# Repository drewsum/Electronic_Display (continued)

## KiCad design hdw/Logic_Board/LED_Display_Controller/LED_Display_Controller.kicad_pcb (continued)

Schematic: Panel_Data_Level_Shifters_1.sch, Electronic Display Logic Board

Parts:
C2601, C2602: 0.1uF; C_0603; Voltage 50V; Digi-Key PN 311-1344-1-ND
C2603, C2604: 10nF; C_0603; Voltage 50V; Digi-Key PN 1276-1921-1-ND
C2605, C2606: 1nF; C_0603; Voltage 50V; Digi-Key PN 1276-1018-1-ND
R2601, R2602, R2603, R2604, R2605, R2606, R2607, R2608, R2609, R2610, R2611, R2612, R2643, R2644, R2645, R2646, R2647, R2648, R2649, R2650, R2651, R2652, R2653, R2654: 100; R_0603; Tolerance 1%; Digi-Key PN A106047CT-ND
R2613, R2614, R2615, R2616, R2617, R2618, R2619, R2620, R2621, R2622, R2623, R2624, R2625, R2626, R2627, R2628, R2629, R2630, R2631, R2632, R2633, R2634, R2635, R2636, R2637, R2638, R2639, R2640, R2641, R2642: 10K; R_0603; Tolerance 1%; Digi-Key PN RMCF0603FT10K0CT-ND
U2601, U2602: 74HCT541; TSSOP-20_4.4x6.5mm_Pitch0.65mm; Digi-Key PN 296-26499-1-ND

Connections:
+3V3: R2613.1, R2614.1; also elsewhere on the board
+5V: C2601.1, C2602.1, C2603.1, C2604.1, C2605.1, C2606.1, U2601.20 (VCC), U2602.20 (VCC); also elsewhere on the board
B0_POS3P3: R2604.1; also elsewhere on the board
B0_POS5: R2646.1; also elsewhere on the board
B1_POS3P3: R2601.1; also elsewhere on the board
B1_POS5: R2643.1; also elsewhere on the board
B2_POS3P3: R2610.1; also elsewhere on the board
B2_POS5: R2652.1; also elsewhere on the board
B3_POS3P3: R2607.1; also elsewhere on the board
B3_POS5: R2649.1; also elsewhere on the board
G0_POS3P3: R2605.1; also elsewhere on the board
G0_POS5: R2647.1; also elsewhere on the board
G1_POS3P3: R2602.1; also elsewhere on the board
G1_POS5: R2644.1; also elsewhere on the board
G2_POS3P3: R2611.1; also elsewhere on the board
G2_POS5: R2653.1; also elsewhere on the board
G3_POS3P3: R2608.1; also elsewhere on the board
G3_POS5: R2650.1; also elsewhere on the board
GND: C2601.2, C2602.2, C2603.2, C2604.2, C2605.2, C2606.2, R2615.2, R2616.2, R2617.2, R2618.2, R2619.2, R2620.2, R2621.2, R2622.2, R2623.2, R2624.2, R2625.2, R2626.2, R2627.2, R2628.2, R2629.2, R2630.2, R2631.2, R2632.2, R2633.2, R2634.2, R2635.2, R2636.2, R2637.2, R2638.2, R2639.2, R2640.2, R2641.2, R2642.2, U2601.10 (GND), U2602.10 (GND); also elsewhere on the board
unnamed: R2601.2, R2615.1, U2601.2 (A0)
unnamed: R2602.2, R2617.1, U2601.3 (A1)
unnamed: R2603.2, R2619.1, U2601.4 (A2)
unnamed: R2604.2, R2621.1, U2601.5 (A3)
unnamed: R2605.2, R2623.1, U2601.6 (A4)
unnamed: R2606.2, R2625.1, U2601.7 (A5)
unnamed: R2607.2, R2616.1, U2602.2 (A0)
unnamed: R2608.2, R2618.1, U2602.3 (A1)
unnamed: R2609.2, R2620.1, U2602.4 (A2)
unnamed: R2610.2, R2622.1, U2602.5 (A3)
unnamed: R2611.2, R2624.1, U2602.6 (A4)
unnamed: R2612.2, R2626.1, U2602.7 (A5)
unnamed: R2627.1, U2601.8 (A6)
unnamed: R2628.1, U2602.8 (A6)
unnamed: R2629.1, U2601.9 (A7)
unnamed: R2630.1, U2602.9 (A7)
unnamed: R2631.1, R2648.2, U2601.13 (Y5)
unnamed: R2632.1, R2654.2, U2602.13 (Y5)
unnamed: R2633.1, R2647.2, U2601.14 (Y4)
unnamed: R2634.1, R2653.2, U2602.14 (Y4)
unnamed: R2635.1, R2646.2, U2601.15 (Y3)
unnamed: R2636.1, R2652.2, U2602.15 (Y3)
unnamed: R2637.1, R2645.2, U2601.16 (Y2)
unnamed: R2638.1, R2651.2, U2602.16 (Y2)
unnamed: R2639.1, R2644.2, U2601.17 (Y1)
unnamed: R2640.1, R2650.2, U2602.17 (Y1)
unnamed: R2641.1, R2643.2, U2601.18 (Y0)
unnamed: R2642.1, R2649.2, U2602.18 (Y0)
R0_POS3P3: R2606.1; also elsewhere on the board
R0_POS5: R2648.1; also elsewhere on the board
R1_POS3P3: R2603.1; also elsewhere on the board
R1_POS5: R2645.1; also elsewhere on the board
R2_POS3P3: R2612.1; also elsewhere on the board
R2_POS5: R2654.1; also elsewhere on the board
R3_POS3P3: R2609.1; also elsewhere on the board
R3_POS5: R2651.1; also elsewhere on the board
~LVL_SHFT_EN: R2613.2, R2614.2, U2601.1 (G1), U2601.19 (G2), U2602.1 (G1), U2602.19 (G2); also elsewhere on the board

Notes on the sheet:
26. Panel Data Level Shifters 1

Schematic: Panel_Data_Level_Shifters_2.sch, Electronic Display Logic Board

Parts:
C2701, C2702: 0.1uF; C_0603; Voltage 50V; Digi-Key PN 311-1344-1-ND
C2703, C2704: 10nF; C_0603; Voltage 50V; Digi-Key PN 1276-1921-1-ND
C2705, C2706: 1nF; C_0603; Voltage 50V; Digi-Key PN 1276-1018-1-ND
R2701, R2702, R2703, R2704, R2705, R2706, R2707, R2708, R2709, R2710, R2711, R2712, R2743, R2744, R2745, R2746, R2747, R2748, R2749, R2750, R2751, R2752, R2753, R2754: 100; R_0603; Tolerance 1%; Digi-Key PN A106047CT-ND
R2713, R2714, R2715, R2716, R2717, R2718, R2719, R2720, R2721, R2722, R2723, R2724, R2725, R2726, R2727, R2728, R2729, R2730, R2731, R2732, R2733, R2734, R2735, R2736, R2737, R2738, R2739, R2740, R2741, R2742: 10K; R_0603; Tolerance 1%; Digi-Key PN RMCF0603FT10K0CT-ND
U2701, U2702: 74HCT541; TSSOP-20_4.4x6.5mm_Pitch0.65mm; Digi-Key PN 296-26499-1-ND

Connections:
+3V3: R2713.1, R2714.1; also elsewhere on the board
+5V: C2701.1, C2702.1, C2703.1, C2704.1, C2705.1, C2706.1, U2701.20 (VCC), U2702.20 (VCC); also elsewhere on the board
B4_POS3P3: R2704.1; also elsewhere on the board
B4_POS5: R2746.1; also elsewhere on the board
B5_POS3P3: R2701.1; also elsewhere on the board
B5_POS5: R2743.1; also elsewhere on the board
B6_POS3P3: R2710.1; also elsewhere on the board
B6_POS5: R2752.1; also elsewhere on the board
B7_POS3P3: R2707.1; also elsewhere on the board
B7_POS5: R2749.1; also elsewhere on the board
G4_POS3P3: R2705.1; also elsewhere on the board
G4_POS5: R2747.1; also elsewhere on the board
G5_POS3P3: R2702.1; also elsewhere on the board
G5_POS5: R2744.1; also elsewhere on the board
G6_POS3P3: R2711.1; also elsewhere on the board
G6_POS5: R2753.1; also elsewhere on the board
G7_POS3P3: R2708.1; also elsewhere on the board
G7_POS5: R2750.1; also elsewhere on the board
GND: C2701.2, C2702.2, C2703.2, C2704.2, C2705.2, C2706.2, R2715.2, R2716.2, R2717.2, R2718.2, R2719.2, R2720.2, R2721.2, R2722.2, R2723.2, R2724.2, R2725.2, R2726.2, R2727.2, R2728.2, R2729.2, R2730.2, R2731.2, R2732.2, R2733.2, R2734.2, R2735.2, R2736.2, R2737.2, R2738.2, R2739.2, R2740.2, R2741.2, R2742.2, U2701.10 (GND), U2702.10 (GND); also elsewhere on the board
unnamed: R2701.2, R2715.1, U2701.2 (A0)
unnamed: R2702.2, R2717.1, U2701.3 (A1)
unnamed: R2703.2, R2719.1, U2701.4 (A2)
unnamed: R2704.2, R2721.1, U2701.5 (A3)
unnamed: R2705.2, R2723.1, U2701.6 (A4)
unnamed: R2706.2, R2725.1, U2701.7 (A5)
unnamed: R2707.2, R2716.1, U2702.2 (A0)
unnamed: R2708.2, R2718.1, U2702.3 (A1)
unnamed: R2709.2, R2720.1, U2702.4 (A2)
unnamed: R2710.2, R2722.1, U2702.5 (A3)
unnamed: R2711.2, R2724.1, U2702.6 (A4)
unnamed: R2712.2, R2726.1, U2702.7 (A5)
unnamed: R2727.1, U2701.8 (A6)
unnamed: R2728.1, U2702.8 (A6)
unnamed: R2729.1, U2701.9 (A7)
unnamed: R2730.1, U2702.9 (A7)
unnamed: R2731.1, R2748.2, U2701.13 (Y5)
unnamed: R2732.1, R2754.2, U2702.13 (Y5)
unnamed: R2733.1, R2747.2, U2701.14 (Y4)
unnamed: R2734.1, R2753.2, U2702.14 (Y4)
unnamed: R2735.1, R2746.2, U2701.15 (Y3)
unnamed: R2736.1, R2752.2, U2702.15 (Y3)
unnamed: R2737.1, R2745.2, U2701.16 (Y2)
unnamed: R2738.1, R2751.2, U2702.16 (Y2)
unnamed: R2739.1, R2744.2, U2701.17 (Y1)
unnamed: R2740.1, R2750.2, U2702.17 (Y1)
unnamed: R2741.1, R2743.2, U2701.18 (Y0)
unnamed: R2742.1, R2749.2, U2702.18 (Y0)
R4_POS3P3: R2706.1; also elsewhere on the board
R4_POS5: R2748.1; also elsewhere on the board
R5_POS3P3: R2703.1; also elsewhere on the board
R5_POS5: R2745.1; also elsewhere on the board
R6_POS3P3: R2712.1; also elsewhere on the board
R6_POS5: R2754.1; also elsewhere on the board
R7_POS3P3: R2709.1; also elsewhere on the board
R7_POS5: R2751.1; also elsewhere on the board
~LVL_SHFT_EN: R2713.2, R2714.2, U2701.1 (G1), U2701.19 (G2), U2702.1 (G1), U2702.19 (G2); also elsewhere on the board

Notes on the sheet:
27. Panel Data Level Shifters 2

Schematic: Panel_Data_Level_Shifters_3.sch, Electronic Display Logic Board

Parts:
C2801, C2802: 0.1uF; C_0603; Voltage 50V; Digi-Key PN 311-1344-1-ND
C2803: 10nF; C_0603; Voltage 50V; Digi-Key PN 1276-1921-1-ND
C2804: 1nF; C_0603; Voltage 50V; Digi-Key PN 1276-1018-1-ND
R2801, R2802, R2805, R2806, R2807, R2808, R2809, R2810, R2811, R2812, R2830, R2831, R2832, R2833, R2834, R2835, R2836, R2837: 100; R_0603; Tolerance 1%; Digi-Key PN A106047CT-ND
R2803, R2804: 10k; R_0603; Tolerance 1%; Digi-Key PN RMCF0603FT10K0CT-ND
R2813, R2814, R2815, R2816, R2817, R2818, R2819, R2820, R2821, R2822, R2823, R2824, R2825, R2826, R2827, R2828, R2829: 10K; R_0603; Tolerance 1%; Digi-Key PN RMCF0603FT10K0CT-ND
U2801: 74LVC1G32; SOT-353_SC-70-5; Digi-Key PN 296-9848-1-ND
U2802: 74HCT541; TSSOP-20_4.4x6.5mm_Pitch0.65mm; Digi-Key PN 296-26499-1-ND

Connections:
+3V3: C2801.1, R2803.1, R2813.1, R2814.1, R2815.1, U2801.5 (VCC); also elsewhere on the board
+5V: C2802.1, C2803.1, C2804.1, R2828.1, R2829.1, U2802.20 (VCC); also elsewhere on the board
GND: C2801.2, C2802.2, C2803.2, C2804.2, R2804.2, R2816.2, R2817.2, R2818.2, R2819.2, R2820.2, R2821.2, R2822.2, R2823.2, R2824.2, R2825.2, R2826.2, R2827.2, U2801.3 (GND), U2802.10 (GND); also elsewhere on the board
unnamed: R2801.2, R2803.2, U2801.1
unnamed: R2802.2, R2804.1, U2801.2
unnamed: R2805.2, R2814.2, U2802.2 (A0)
unnamed: R2806.2, R2815.2, U2802.3 (A1)
unnamed: R2807.2, R2816.1, U2802.4 (A2)
unnamed: R2808.2, R2817.1, U2802.5 (A3)
unnamed: R2809.2, R2818.1, U2802.6 (A4)
unnamed: R2810.2, R2819.1, U2802.7 (A5)
unnamed: R2811.2, R2820.1, U2802.8 (A6)
unnamed: R2812.2, R2821.1, U2802.9 (A7)
unnamed: R2822.1, R2837.2, U2802.11 (Y7)
unnamed: R2823.1, R2836.2, U2802.12 (Y6)
unnamed: R2824.1, R2835.2, U2802.13 (Y5)
unnamed: R2825.1, R2834.2, U2802.14 (Y4)
unnamed: R2826.1, R2833.2, U2802.15 (Y3)
unnamed: R2827.1, R2832.2, U2802.16 (Y2)
unnamed: R2828.2, R2831.2, U2802.17 (Y1)
unnamed: R2829.2, R2830.2, U2802.18 (Y0)
Panel_CLK_POS3P3: R2807.1; also elsewhere on the board
Panel_CLK_POS5: R2832.1; also elsewhere on the board
Panel_Dim_PWM: R2802.1; also elsewhere on the board
Panel_LAT_POS3P3: R2806.1; also elsewhere on the board
Panel_LAT_POS5: R2831.1; also elsewhere on the board
Row_A_POS3P3: R2811.1; also elsewhere on the board
Row_A_POS5: R2836.1; also elsewhere on the board
Row_B_POS3P3: R2810.1; also elsewhere on the board
Row_B_POS5: R2835.1; also elsewhere on the board
Row_C_POS3P3: R2809.1; also elsewhere on the board
Row_C_POS5: R2834.1; also elsewhere on the board
Row_D_POS3P3: R2808.1; also elsewhere on the board
Row_D_POS5: R2833.1; also elsewhere on the board
Row_E_POS3P3: R2812.1; also elsewhere on the board
Row_E_POS5: R2837.1; also elsewhere on the board
~LVL_SHFT_EN: R2813.2, U2802.1 (G1), U2802.19 (G2); also elsewhere on the board
~Panel_OE_Dim_POS3P3: R2805.1, U2801.4
~Panel_OE_POS3P3: R2801.1; also elsewhere on the board
~Panel_OE_POS5: R2830.1; also elsewhere on the board

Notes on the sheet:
28. Panel Data Level Shifters 3

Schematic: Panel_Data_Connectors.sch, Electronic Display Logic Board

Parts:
D2901, D2902, D2903, D2904, D2905, D2906, D2907, D2908, D2909, D2910, D2911, D2912: SP0505BAJT; SOT-363_SC-70-6; Digi-Key PN F3160CT-ND
J2901: STRING 1; IDC-Header_2x08_Pitch2.54mm_Straight; Digi-Key PN ED10523-ND
J2902: STRING 2; IDC-Header_2x08_Pitch2.54mm_Straight; Digi-Key PN ED10523-ND
J2903: STRING 3; IDC-Header_2x08_Pitch2.54mm_Straight; Digi-Key PN ED10523-ND
J2904: STRING 4; IDC-Header_2x08_Pitch2.54mm_Straight; Digi-Key PN ED10523-ND

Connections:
B0_POS5: D2901.6 (K), J2901.3; also elsewhere on the board
B1_POS5: D2902.1 (K), J2901.7; also elsewhere on the board
B2_POS5: D2904.6 (K), J2902.3; also elsewhere on the board
B3_POS5: D2905.1 (K), J2902.7; also elsewhere on the board
B4_POS5: D2907.6 (K), J2903.3; also elsewhere on the board
B5_POS5: D2908.1 (K), J2903.7; also elsewhere on the board
B6_POS5: D2910.6 (K), J2904.3; also elsewhere on the board
B7_POS5: D2911.1 (K), J2904.7; also elsewhere on the board
G0_POS5: D2901.1 (K), J2901.2; also elsewhere on the board
G1_POS5: D2901.5 (K), J2901.6; also elsewhere on the board
G2_POS5: D2904.1 (K), J2902.2; also elsewhere on the board
G3_POS5: D2904.5 (K), J2902.6; also elsewhere on the board
G4_POS5: D2907.1 (K), J2903.2; also elsewhere on the board
G5_POS5: D2907.5 (K), J2903.6; also elsewhere on the board
G6_POS5: D2910.1 (K), J2904.2; also elsewhere on the board
G7_POS5: D2910.5 (K), J2904.6; also elsewhere on the board
GND: D2901.2 (A), D2902.2 (A), D2903.2 (A), D2904.2 (A), D2905.2 (A), D2906.2 (A), D2907.2 (A), D2908.2 (A), D2909.2 (A), D2910.2 (A), D2911.2 (A), D2912.2 (A), J2901.4, J2901.16, J2902.4, J2902.16, J2903.4, J2903.16, J2904.4, J2904.16; also elsewhere on the board
Panel_CLK_POS5: D2903.4 (K), D2906.4 (K), D2909.4 (K), D2912.4 (K), J2901.13, J2902.13, J2903.13, J2904.13; also elsewhere on the board
Panel_LAT_POS5: D2903.1 (K), D2906.1 (K), D2909.1 (K), D2912.1 (K), J2901.14, J2902.14, J2903.14, J2904.14; also elsewhere on the board
R0_POS5: D2901.3 (K), J2901.1; also elsewhere on the board
R1_POS5: D2901.4 (K), J2901.5; also elsewhere on the board
R2_POS5: D2904.3 (K), J2902.1; also elsewhere on the board
R3_POS5: D2904.4 (K), J2902.5; also elsewhere on the board
R4_POS5: D2907.3 (K), J2903.1; also elsewhere on the board
R5_POS5: D2907.4 (K), J2903.5; also elsewhere on the board
R6_POS5: D2910.3 (K), J2904.1; also elsewhere on the board
R7_POS5: D2910.4 (K), J2904.5; also elsewhere on the board
Row_A_POS5: D2902.6 (K), D2905.6 (K), D2908.6 (K), D2911.6 (K), J2901.9, J2902.9, J2903.9, J2904.9; also elsewhere on the board
Row_B_POS5: D2902.5 (K), D2905.5 (K), D2908.5 (K), D2911.5 (K), J2901.10, J2902.10, J2903.10, J2904.10; also elsewhere on the board
Row_C_POS5: D2903.3 (K), D2906.3 (K), D2909.3 (K), D2912.3 (K), J2901.11, J2902.11, J2903.11, J2904.11; also elsewhere on the board
Row_D_POS5: D2902.4 (K), D2905.4 (K), D2908.4 (K), D2911.4 (K), J2901.12, J2902.12, J2903.12, J2904.12; also elsewhere on the board
Row_E_POS5: D2902.3 (K), D2905.3 (K), D2908.3 (K), D2911.3 (K), J2901.8, J2902.8, J2903.8, J2904.8; also elsewhere on the board
~Panel_OE_POS5: D2903.6 (K), D2906.6 (K), D2909.6 (K), D2912.6 (K), J2901.15, J2902.15, J2903.15, J2904.15; also elsewhere on the board

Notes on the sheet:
String 1 is the top string, String 4 is the bottom string. Each string is 5 panels long Each panel is 64x64 pixels This yields a 320x256 pixel overall display resolution
29. Panel Data Connectors

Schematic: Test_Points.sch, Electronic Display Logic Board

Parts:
J3001: USB UART; Pin_Header_Straight_1x03_Pitch2.54mm
J3002: WIFI UART; Pin_Header_Straight_1x03_Pitch2.54mm
J3003: FLASH SPI; Pin_Header_Straight_1x04_Pitch2.54mm
TP3001, TP3007, TP3009, TP3010: TP; Pin_Header_Angled_1x01_Pitch2.54mm
TP3002, TP3003, TP3004, TP3005, TP3006, TP3008: TP; Measurement_Point_Round-SMD-Pad_Small

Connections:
+3V3: TP3004.1; also elsewhere on the board
+5.5V: TP3006.1; also elsewhere on the board
+5V: TP3005.1; also elsewhere on the board
+5V_USB: TP3008.1; also elsewhere on the board
+12V: TP3003.1; also elsewhere on the board
+12Vin: TP3002.1; also elsewhere on the board
FLASH_MISO: J3003.2; also elsewhere on the board
FLASH_MOSI: J3003.1; also elsewhere on the board
FLASH_SCK: J3003.3; also elsewhere on the board
GND: J3001.3, J3002.3, J3003.4, TP3001.1, TP3009.1, TP3010.1; also elsewhere on the board
GND_USB: TP3007.1; also elsewhere on the board
USB_UART_RX: J3001.2; also elsewhere on the board
USB_UART_TX: J3001.1; also elsewhere on the board
WIFI_UART_RX: J3002.2; also elsewhere on the board
WIFI_UART_TX: J3002.1; also elsewhere on the board

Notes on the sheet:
30. Test Points

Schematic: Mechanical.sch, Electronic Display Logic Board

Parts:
H3101, H3102, H3103, H3104, H3105, H3106, H3107, H3108, H3109, H3110, H3111, H3112: 3mm Mounting Hole; MountingHole_3mm_Pad_Via
MK3101, MK3102, MK3105, MK3106, MK3109, MK3110, MK3113, MK3114, MK3117, MK3118, MK3121, MK3122: 4-40 Standoff; Digi-Key PN 36-2204-ND
MK3103, MK3104, MK3107, MK3108, MK3111, MK3112, MK3115, MK3116, MK3119, MK3120, MK3123, MK3124: 4-40 Screw; Digi-Key PN 36-9900-ND

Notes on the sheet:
31. Mechanical

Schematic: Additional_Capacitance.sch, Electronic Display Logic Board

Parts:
C3201, C3202, C3203: 100uF; CP_Tantalum_Case-B_EIA-3528-21_Reflow; Voltage 6.3V; Tolerance 20%; Digi-Key PN 478-3130-1-ND
C3204, C3205, C3206, C3207, C3208, C3209, C3210, C3211, C3212, C3213, C3214, C3215, C3216, C3217, C3218, C3219: 330pF; C_0603; Voltage 50V; Digi-Key PN 399-6880-1-ND

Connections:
+3V3: C3201.1, C3204.2, C3205.2, C3206.2, C3207.2, C3208.2, C3209.2, C3210.2, C3211.2, C3212.2, C3213.2, C3214.2, C3215.2, C3216.2, C3217.2, C3218.2, C3219.2; also elsewhere on the board
+5V: C3202.1, C3203.1, C3204.1, C3205.1, C3206.1, C3207.1, C3208.1, C3209.1, C3210.1, C3211.1, C3212.1, C3213.1, C3214.1, C3215.1, C3216.1, C3217.1, C3218.1, C3219.1; also elsewhere on the board
GND: C3201.2, C3202.2, C3203.2; also elsewhere on the board

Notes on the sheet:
32. Additional Capacitance
Bulk Capacitors
Stitching Capacitors

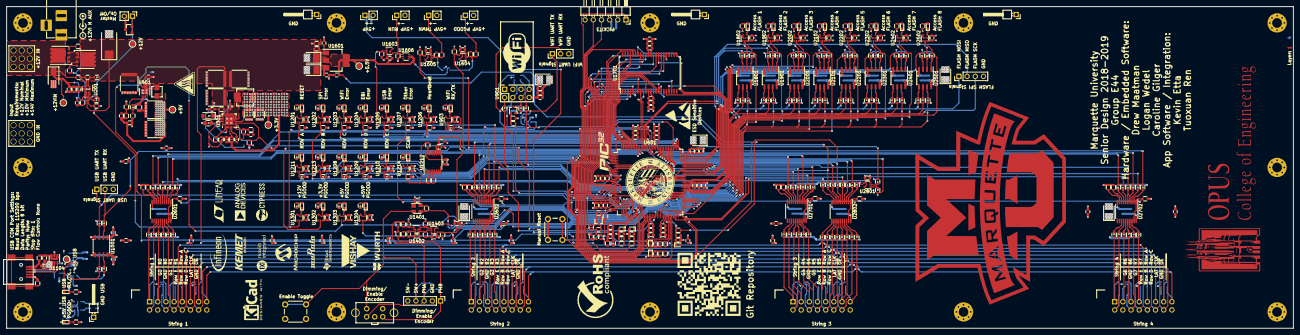
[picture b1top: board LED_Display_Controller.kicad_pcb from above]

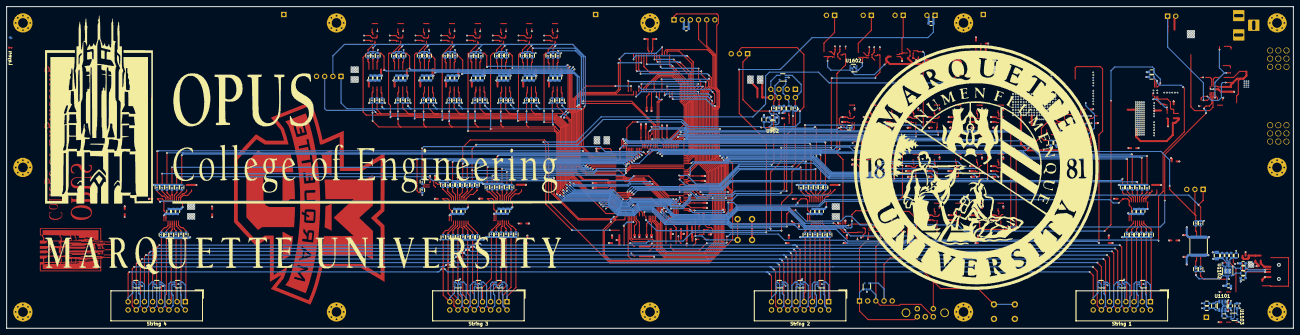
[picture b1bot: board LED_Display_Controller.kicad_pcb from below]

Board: 4 copper layers, 400.0 x 100.0 mm, 720 parts (122 on the bottom side), 405 nets.

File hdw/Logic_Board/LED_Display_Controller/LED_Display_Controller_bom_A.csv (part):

Component,Description,Part,References,Value,Footprint,Quantity Per PCB,Datasheet,Digi-Key PN,display_footprint,Dielectric,Voltage,Tolerance,Baud_Rate,Parity,Data_Length,Flow_Control,Stop_Bits,Ampacity,Config,Wattage
1,Unpolarized capacitor,C_Custom,C201 C204 C305 C307 C403 C405 C501 C502 C601 C602 C603 C611 C612 C613 C620 C621 C622 C902 C905 C906 C907 C1001 C1003 C1101 C1102 C1103 C1104 C1105 C1107 C1108 C1111 C1201 C1202 C1203 C1204 C1205 C1206 C1207 C1208 C1209 C1210 C1211 C1212 C1213 C1214 C1301 C1302 C1303 C1304 C1401 C1402 C1403 C1404 C1405 C1602 C1603 C1604 C1605 C1607 C1608 C1609 C1701 C1704 C1801 C1804 C1901 C1904 C2001 C2004 C2101 C2104 C2201 C2204 C2301 C2304 C2401 C2404 C2501 C2504 C2601 C2602 C2701 C2702 C2801 C2802,0.1uF,C_0603,85,,311-1344-1-ND,603,X7R,50V,,,,,,,,,
2,Unpolarized capacitor,C_Custom,C1002,0.56uF,C_2220,1,,565-4707-1-ND,2220,X7R,250VAC,,,,,,,,,
3,Polarised capacitor,CP_Tant_Custom,C604 C901 C1606 C3201 C3202 C3203,100uF,CP_Tantalum_Case-B_EIA-3528-21_Reflow,6,,478-3130-1-ND,3528,,6.3V,20%,,,,,,,,
4,Polarised capacitor,CP_Tant_Custom,C205,100uF,CP_Tantalum_Case-X_EIA-7343-43_Reflow,1,,718-1102-1-ND,7343,,16V,10%,,,,,,,,
5,Unpolarized capacitor,C_Custom,C202 C304 C605 C606 C607 C614 C615 C616 C623 C624 C625 C903 C1702 C1705 C1802 C1902 C2002 C2102 C2202 C2302 C2402 C2502 C2603 C2604 C2703 C2704 C2803,10nF,C_0603,27,,1276-1921-1-ND,603,X7R,50V,,,,,,,,,
6,Polarised capacitor,CP_Tant_Custom,C1601,10uF,CP_Tantalum_Case-B_EIA-3528-21_Reflow,1,,478-8236-1-ND,3528,,16V,10%,,,,,,,,
7,Unpolarized capacitor,C_Custom,C308 C310,15pF,C_0603,2,,478-10289-1-ND,603,NP0,50V,,,,,,,,,
8,Unpolarized capacitor,C_Custom,C203 C608 C609 C610 C617 C618 C619 C626 C627 C628 C904 C1703 C1706 C1803 C1903 C2003 C2103 C2203 C2303 C2403 C2503 C2605 C2606 C2705 C2706 C2804,1nF,C_0603,26,,1276-1018-1-ND,603,X7R,50V,,,,,,,,,
9,Unpolarized capacitor,C_Custom,C309 C401,2.2uF,C_0805,2,,445-5691-1-ND,805,X7R,16V,,,,,,,,,
10,Unpolarized capacitor,C_Custom,C301 C302 C303 C402 C406 C407,22uF,C_2220,6,,445-1453-1-ND,2220,X7R,25V,,,,,,,,,
11,Unpolarized capacitor,C_Custom,C1501 C1502 C1503 C1504 C1505 C3204 C3205 C3206 C3207 C3208 C3209 C3210 C3211 C3212 C3213 C3214 C3215 C3216 C3217 C3218 C3219,330pF,C_0603,21,,399-6880-1-ND,603,NP0,50V,,,,,,,,,
12,Unpolarized capacitor,C_Custom,C404,33pF,C_0603,1,,399-1055-1-ND,603,NP0,50V,,,,,,,,,
13,Unpolarized capacitor,C_Custom,C1106,4.7uF,C_0805,1,,1276-2972-1-ND,805,X7R,10V,,,,,,,,,
14,Unpolarized capacitor,C_Custom,C1109 C1110,47pF,C_0603,2,,478-1171-1-ND,603,NP0,50V,,,,,,,,,
15,Unpolarized capacitor,C_Custom,C311 C312,47uF,C_1210,2,,490-4844-1-ND,1210,X7R,6.3V,,,,,,,,,
16,Unpolarized capacitor,C_Custom,C306,62pF,C_0603,1,,1276-2320-1-ND,603,NP0,50V,,,,,,,,,
17,"Bidirectional transient-voltage-suppression diode, filled shape",D_TVS_ALT,D202,24V,D_SMA,1,~,SMAJ24CALFCT-ND,,,,,,,,,,,,
18,"300mW Zener Diode, SOD-523",MM5Zxx,D1501 D1502 D1503 D1504 D1505,BZT52C3V3T,D_SOD-523,5,https://diotec.com/tl_files/diotec/files/pdf/datasheets/mm5z2v4.pdf,BZT52C3V3T-TPMSCT-ND,,,,,,,,,,,,
19,Light emitting diode,LED,D902 D1101 D1206 D1208 D1209 D1210 D1211 D1212 D1213 D1301 D1302 D1303 D1304 D1801 D1901 D2001 D2101 D2201 D2301 D2401 D2501,Green,LED_0603,21,~,160-1446-1-ND,,,,,,,,,,,,
20,"40V 0.35A Small Signal Schottky Diode, SOD-123",MBR0530,D301,MBR0530,D_SOD-123,1,http://www.mccsemi.com/up_pdf/MBR0520~MBR0580(SOD123).pdf,MBR0530T1GOSCT-ND,,,,,,,,,,,,
21,"Dual Line CAN Bus Protector, 24Vrwm",NUP2105L,D201,NUP2105L,SOT-23,1,http://www.onsemi.com/pub_link/Collateral/NUP2105L-D.PDF,NUP2105LT1GOSCT-ND,,,,,,,,,,,,
22,"Low capacitance unidirectional quadruple ESD protection diode array, 3.3V, Common Anode, SOT-353",PESD3V3L4UG,D901 D1401,PESD3V3L4UG,SOT-353_SC-70-5,2,http://www.nxp.com/documents/data_sheet/PESDXL4UF_G_W.pdf,1727-3827-1-ND,,,,,,,,,,,,
23,Light emitting diode,LED,D1201 D1202 D1203 D1204 D1205 D1207,Red,LED_0603,6,~,160-1447-1-ND,,,,,,,,,,,,
24,"TVS Diode Array, 5.5V Standoff, 5 Channels, SC-70-6 package",SP0505BAJT,D2901 D2902 D2903 D2904 D2905 D2906 D2907 D2908 D2909 D2910 D2911 D2912,SP0505BAJT,SOT-363_SC-70-6,12,http://www.littelfuse.com/~/media/files/littelfuse/technical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,F3160CT-ND,,,,,,,,,,,,
25,Light emitting diode,LED,D1102,Yellow,LED_0603,1,~,160-1448-1-ND,,,,,,,,,,,,
26,,COM_Port_Settings,DOC1101,COM_Port_Settings,,1,,,,,,,921600 bps,None,8 bit,None,1,,,
27,"Generic screw terminal, single row, 01x01, script generated (kicad-library-utils/schlib/autogen/connector/)",Screw_Terminal_01x01,J201,+12V IN,Wuerth_7461096_M4_Shank_9pos,1,~,732-3214-ND,,,,,,,,,,,,
28,DC Barrel Jack with an internal switch,Barrel_Jack_Switch,J203,+12V IN AUX,BARREL_JACK,1,~,CP-202BH-ND,,,,,,,,,,,,
29,"Generic connector, single row, 01x05, script generated (kicad-library-utils/schlib/autogen/connector/)",Conn_01x05,J1401,Encoder Ext,Pin_Header_Straight_1x05_Pitch2.54mm,1,~,,,,,,,,,,,,,
30,"Generic connector, single row, 01x04, script generated (kicad-library-utils/schlib/autogen/connector/)",Conn_01x04,J3003,FLASH SPI,Pin_Header_Straight_1x04_Pitch2.54mm,1,~,,,,,,,,,,,,,
31,"Generic screw terminal, single row, 01x01, script generated (kicad-library-utils/schlib/autogen/connector/)",Screw_Terminal_01x01,J202,GND IN,Wuerth_7461096_M4_Shank_9pos,1,~,732-3214-ND,,,,,,,,,,,,
32,"Generic connector, double row, 02x01, this symbol is compatible with counter-clockwise, top-bottom and odd-even numbering schemes., script generated (kicad-library-utils/schlib/autogen/connector/)",Conn_02x01,J204,Master Power SW,Pin_Header_Straight_1x02_Pitch2.54mm,1,~,,,,,,,,,,,,,
33,"Generic connector, single row, 01x06, script generated (kicad-library-utils/schlib/autogen/connector/)",Conn_01x06,J501,PICKIT3,PICKIT3_Header,1,~,,,,,,,,,,,,,
34,"Generic connector, single row, 01x02, script generated (kicad-library-utils/schlib/autogen/connector/)",Conn_01x02,J1601,POS5P EXT,Pin_Header_Straight_1x02_Pitch2.54mm,1,~,,,,,,,,,,,,,
35,"Generic connector, single row, 01x02, script generated (kicad-library-utils/schlib/autogen/connector/)",Conn_01x02,J1602,POS5P PGOOD,Pin_Header_Straight_1x02_Pitch2.54mm,1,~,,,,,,,,,,,,,
36,"Generic connector, single row, 01x02, script generated (kicad-library-utils/schlib/autogen/connector/)",Conn_01x02,J1604,POS5P_RUN,Pin_Header_Straight_1x02_Pitch2.54mm,1,~,,,,,,,,,,,,,
37,"Generic connector, single row, 01x02, script generated (kicad-library-utils/schlib/autogen/connector/)",Conn_01x02,J1603,POS5P_THWN,Pin_Header_Straight_1x02_Pitch2.54mm,1,~,,,,,,,,,,,,,
38,"Generic connector, double row, 02x08, odd/even pin numbering scheme (row 1 odd numbers, row 2 even numbers), script generated (kicad-library-utils/schlib/autogen/connector/)",Conn_02x08_Odd_Even,J2901,STRING 1,IDC-Header_2x08_Pitch2.54mm_Straight,1,~,ED10523-ND,,,,,,,,,,,,
39,"Generic connector, double row, 02x08, odd/even pin numbering scheme (row 1 odd numbers, row 2 even numbers), script generated (kicad-library-utils/schlib/autogen/connector/)",Conn_02x08_Odd_Even,J2902,STRING 2,IDC-Header_2x08_Pitch2.54mm_Straight,1,~,ED10523-ND,,,,,,,,,,,,
40,"Generic connector, double row, 02x08, odd/even pin numbering scheme (row 1 odd numbers, row 2 even numbers), script generated (kicad-library-utils/schlib/autogen/connector/)",Conn_02x08_Odd_Even,J2903,STRING 3,IDC-Header_2x08_Pitch2.54mm_Straight,1,~,ED10523-ND,,,,,,,,,,,,
41,"Generic connector, double row, 02x08, odd/even pin numbering scheme (row 1 odd numbers, row 2 even numbers), script generated (kicad-library-utils/schlib/autogen/connector/)",Conn_02x08_Odd_Even,J2904,STRING 4,IDC-Header_2x08_Pitch2.54mm_Straight,1,~,ED10523-ND,,,,,,,,,,,,
42,"Generic connector, single row, 01x03, script generated (kicad-library-utils/schlib/autogen/connector/)",Conn_01x03,J3001,USB UART,Pin_Header_Straight_1x03_Pitch2.54mm,1,~,,,,,,,,,,,,,
43,USB Micro Type B connector,USB_B_Mini,J1101,USB_B_Mini,USB_Mini-B,1,~,732-2109-1-ND,,,,,,,,,,,,
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
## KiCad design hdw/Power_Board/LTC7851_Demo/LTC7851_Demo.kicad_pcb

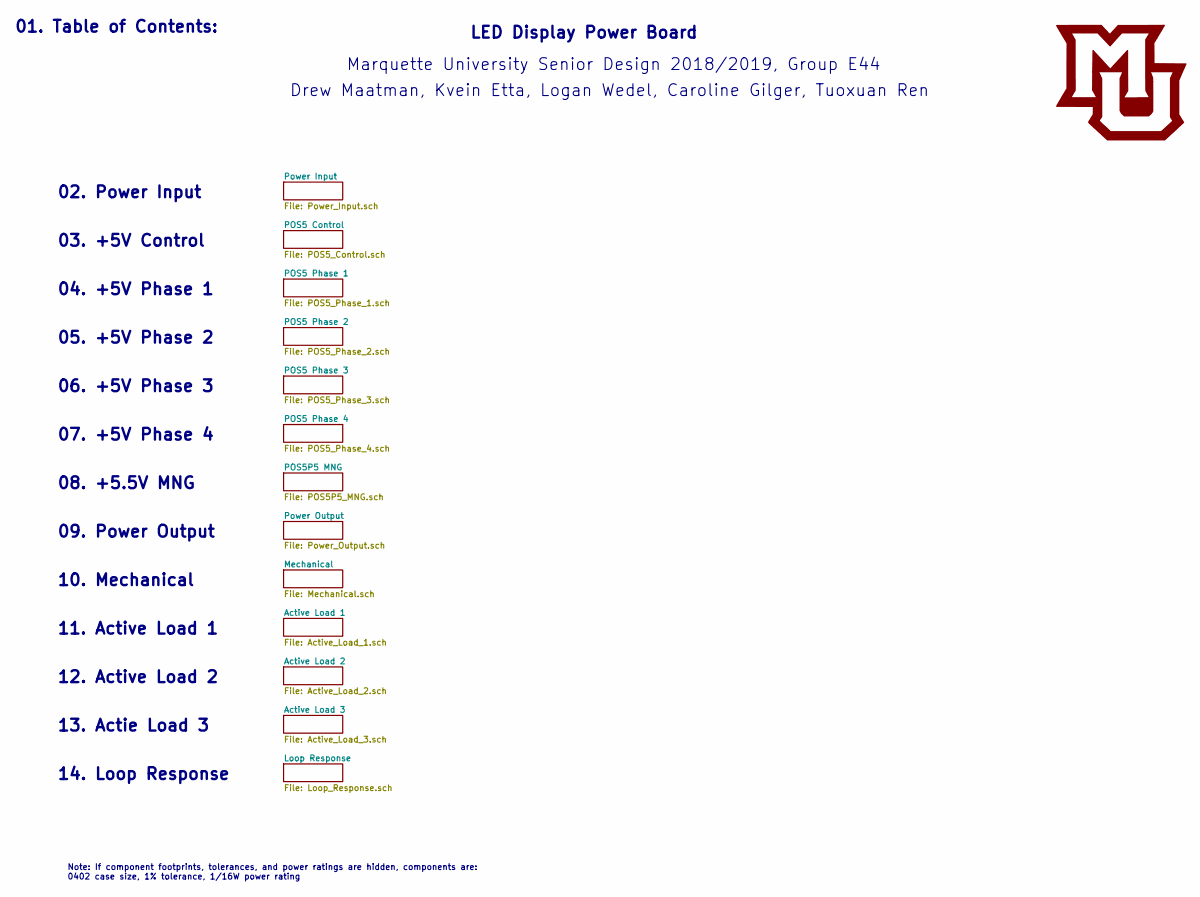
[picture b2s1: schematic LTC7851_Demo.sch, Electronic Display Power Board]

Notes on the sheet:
01. Table of Contents:
LED Display Power Board
Marquette University Senior Design 2018/2019, Group E44
Drew Maatman, Kvein Etta, Logan Wedel, Caroline Gilger, Tuoxuan Ren
02. Power Input
03. +5V Control
04. +5V Phase 1
05. +5V Phase 2
06. +5V Phase 3
07. +5V Phase 4
08. +5.5V MNG
09. Power Output
10. Mechanical
11. Active Load 1
12. Active Load 2
13. Actie Load 3
14. Loop Response
Note: If component footprints, tolerances, and power ratings are hidden, components are: 0402 case size, 1% tolerance, 1/16W power rating

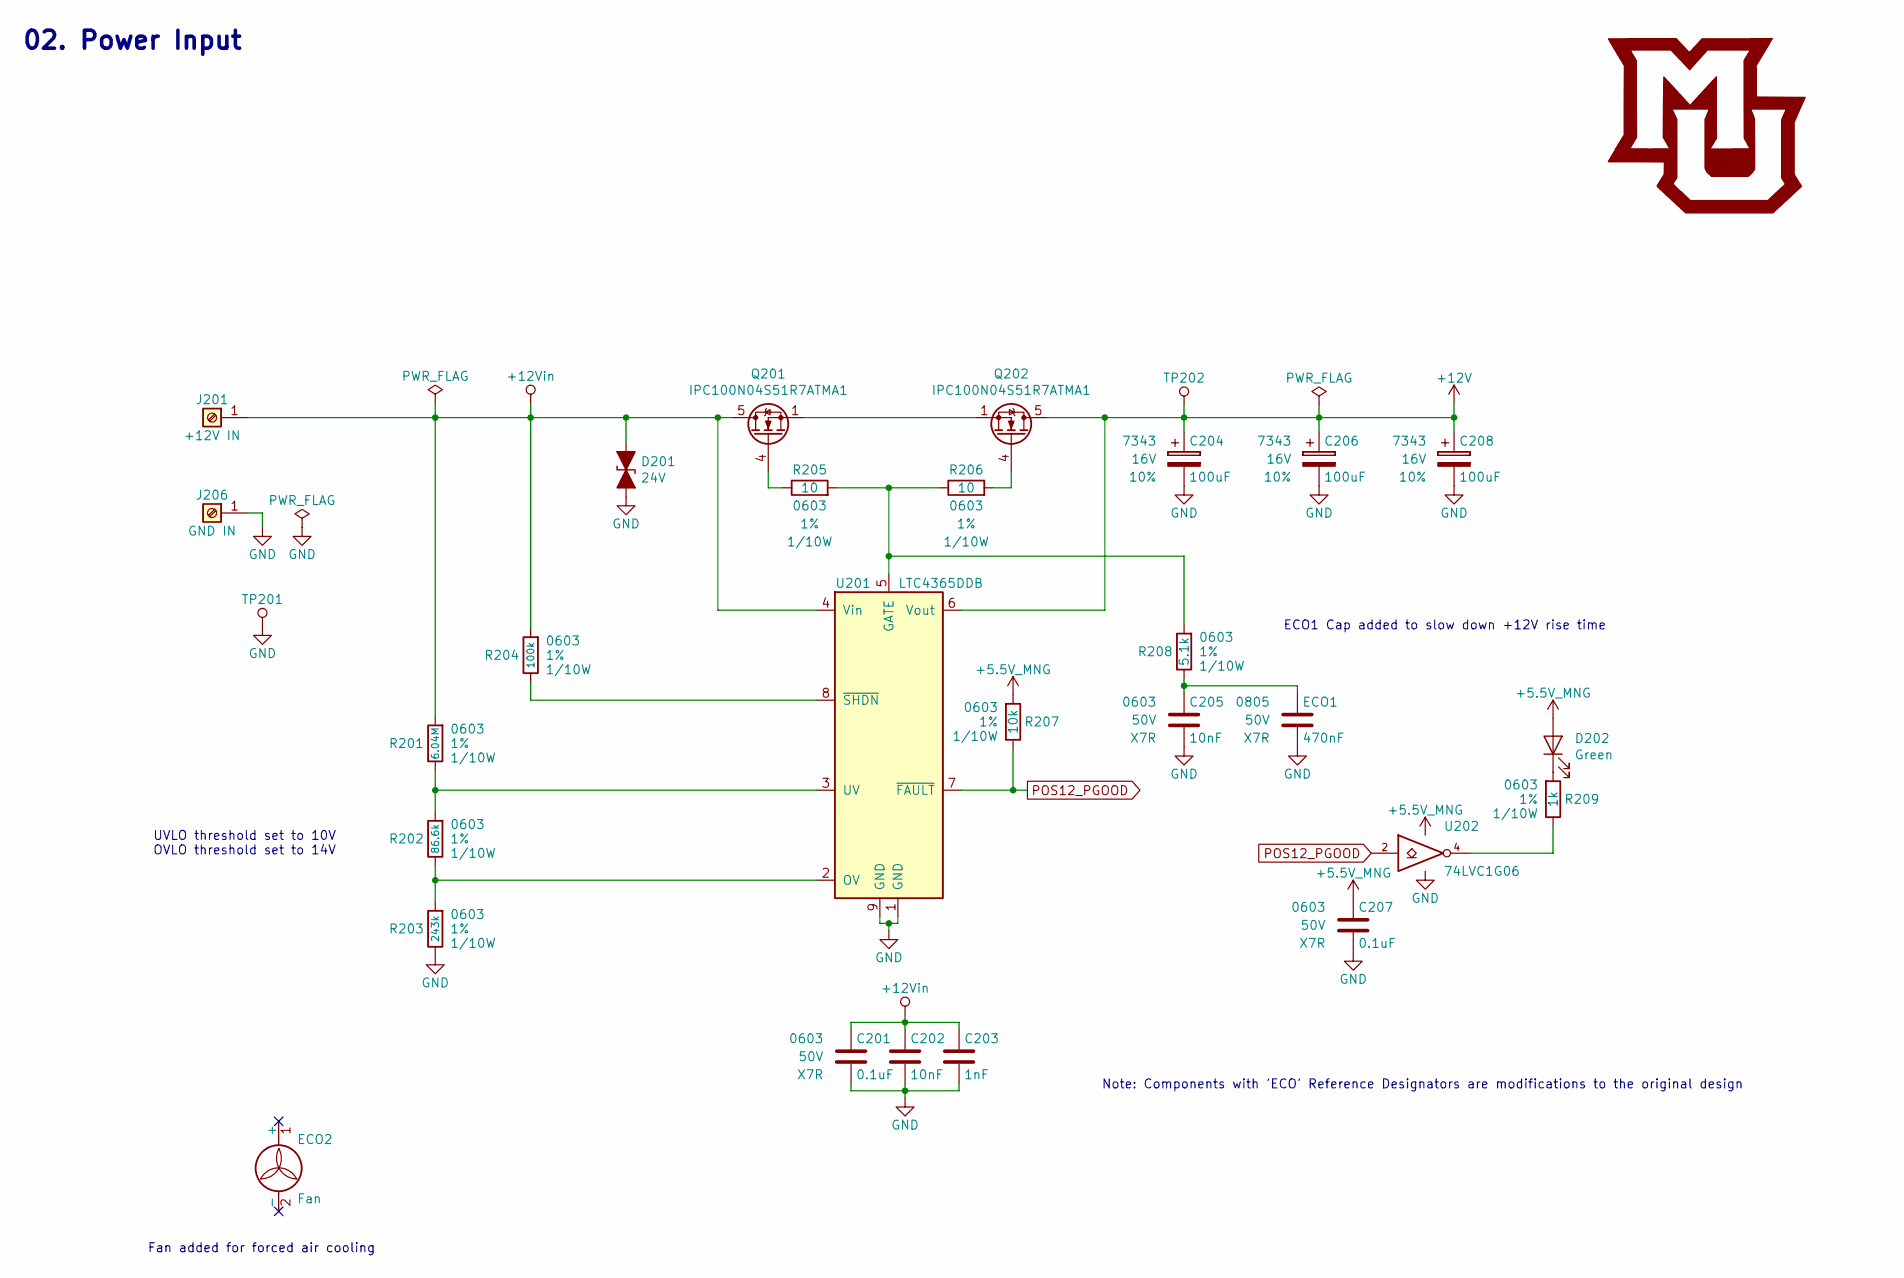
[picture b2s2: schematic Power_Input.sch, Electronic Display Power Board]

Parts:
C201, C207: 0.1uF; C_0603; Voltage 50V; Digi-Key PN 490-4779-1-ND
C202, C205: 10nF; C_0603; Voltage 50V; Digi-Key PN 1276-1921-1-ND
C203: 1nF; C_0603; Voltage 50V; Digi-Key PN 311-1080-1-ND
C204, C206, C208: 100uF; CP_Tantalum_Case-X_EIA-7343-43_Reflow; Voltage 16V; Tolerance 10%; Digi-Key PN 718-1102-1-ND
D201: 24V; D_SMA; Digi-Key PN SMAJ24CALFCT-ND
D202: Green; LED_0603; Digi-Key PN 160-1446-1-ND
ECO1: 470nF; Voltage 50V
ECO2: Fan
J201: +12V IN; Wuerth_7461096_M4_Shank_9pos; Digi-Key PN 732-3214-ND
J206: GND IN; Wuerth_7461096_M4_Shank_9pos; Digi-Key PN 732-3214-ND
Q201, Q202: IPC100N04S51R7ATMA1; TDSON-8-1; Digi-Key PN BSC123N10LSGATMA1CT-ND
R201: 6.04M; R_0603; Tolerance 1%; Digi-Key PN 541-6.04MHCT-ND
R202: 86.6k; R_0603; Tolerance 1%; Digi-Key PN 311-86.6KHRCT-ND
R203: 243k; R_0603; Tolerance 1%; Digi-Key PN 541-243KHCT-ND
R204: 100k; R_0603; Tolerance 1%; Digi-Key PN P100KHCT-ND
R205, R206: 10; R_0603; Tolerance 1%; Digi-Key PN YAG3351CT-ND
R207: 10k; R_0603; Tolerance 1%; Digi-Key PN RHM10KADCT-ND
R208: 5.1k; R_0603; Tolerance 1%; Digi-Key PN RMCF0603FT5K10CT-ND
R209: 1k; R_0603; Tolerance 1%; Digi-Key PN RHM1.0KDCT-ND
TP201: TP; Pin_Header_Angled_1x01_Pitch2.54mm
TP202: TP; Measurement_Point_Round-SMD-Pad_Small
U201: LTC4365DDB; DFN-8-1EP_2x3mm_Pitch0.5mm; Digi-Key PN LTC4365IDDB#TRMPBFCT-ND
U202: 74LVC1G06; SOT-353_SC-70-5; Digi-Key PN 296-8484-1-ND

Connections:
+5.5V_MNG: C207.1, D202.2 (A), R207.1, U202.5 (VCC); also elsewhere on the board
+12V: C204.1, C206.1, C208.1, Q202.5 (D), TP202.1, U201.6 (Vout); also elsewhere on the board
+12Vin: C201.1, C202.1, C203.1, D201.1 (A1), J201.1, Q201.5 (D), R201.1, R204.1, U201.4 (Vin)
GND: C201.2, C202.2, C203.2, C204.2, C205.2, C206.2, C207.2, C208.2, D201.2 (A2), ECO1.2, J206.1, R203.2, TP201.1, U201.1 (GND), U201.9 (GND), U202.3 (GND); also elsewhere on the board
unnamed: C205.1, ECO1.1, R208.2
unnamed: D202.1 (K), R209.1
unnamed: Q201.1 (S), Q201.2 (S), Q201.3 (S), Q202.1 (S), Q202.2 (S), Q202.3 (S)
unnamed: Q201.4 (G), R205.2
unnamed: Q202.4 (G), R206.1
unnamed: R201.2, R202.1, U201.3 (UV)
unnamed: R202.2, R203.1, U201.2 (OV)
unnamed: R204.2, U201.8 (~SHDN)
unnamed: R205.1, R206.2, R208.1, U201.5 (GATE)
unnamed: R209.2, U202.4
POS12_PGOOD: R207.2, U201.7 (~FAULT), U202.2

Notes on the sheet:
02. Power Input
ECO1 Cap added to slow down +12V rise time
Fan added for forced air cooling
Note: Components with 'ECO' Reference Designators are modifications to the original design
UVLO threshold set to 10V OVLO threshold set to 14V
